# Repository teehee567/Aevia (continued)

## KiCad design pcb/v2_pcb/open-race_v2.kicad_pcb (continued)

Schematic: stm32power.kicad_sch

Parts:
C28, C36, C39, C40, C46, C47, C48, C50, C52, C54, C55, C58, C59, C64, C66, C67, C71, C72, C73, C74, C75, C76, C77, C78, C79, C80, C169, C309: 100nF 50V X7R; C_0402_1005Metric; Voltage 50 VDC; Tolerance ±10%; MPN CGA2B3X7R1H104K050BE
C29, C35: 10uF 10V X7R; C_0805_2012Metric; Voltage 10 VDC; Tolerance ±10%; MPN GCJ21BR71A106KE01L
C34: 4.7uF 16V X7S; C_0603_1608Metric; Voltage 16 VDC; Tolerance ±10%; MPN GCM188C71C475KE36D
C37: 2.2nF 50V X7R; C_0402_1005Metric; Voltage 50 VDC; Tolerance ±10%; MPN CGA2B2X7R1H222K050BE
C38, C41, C43, C44, C45, C51, C57, C60, C61, C63, C65, C68, C69, C70, C308: 1uF 10V X7S; C_0402_1005Metric; Voltage 10 VDC; Tolerance ±10%; MPN GCM155C71A105KE38D
C170, C176, C177, C178, C179: 22uF 6.3V X7T; C_0805_2012Metric; Voltage 6.3 VDC; Tolerance ±20%; MPN GCJ21BD70J226ME02L
L4: 2.2nH 1A; L_TDK_MHQ1005_1.0x0.6mm; MPN MHQ1005P2N2BT000
L7: 1uH; L_1008_2520Metric; MPN DFE252012P-1R0M=P2
L8: 22R @100MHz 8A; L_0603_1608Metric; MPN BLM18SN220TN1D
R22, R167: 0R; R_1206_3216Metric; Tolerance Jumper; MPN WFZ120600000ZE66
R27: 0R; R_0402_1005Metric; Tolerance Jumper; MPN RC0402JR-070RL
R148, R159: 0R; R_0402_1005Metric; Tolerance Jumper; MPN CRCW04020000Z0ED
R168: 50mR (DNP); R_2512_6332Metric
R173: 0R DNP (alternate to L8); R_0402_1005Metric
R220: 2R; R_0402_1005Metric; Tolerance ±1%; MPN RCS04022R00FKED
U1: STM32N657X0H3Q; VFBGA264_14X14_STM

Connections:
+1V8_AON: C36.2, R148.1; also elsewhere on the board
+1V8_RUN: C38.2, C39.2, C46.2, C47.2, C50.2, C54.2, C71.2, C74.2, C77.2, C78.2, C79.2, C80.2, L4.1, L8.1, R27.1, R173.2, U1.C5 (VDDA18USB), U1.L13 (VDDIO2), U1.L14 (VDDIO2), U1.M5 (VDDA18PLL), U1.M14 (VDDIO2), U1.M15 (VDDIO2), U1.N6 (VDDA18ADC), U1.N13 (VDDIO3), U1.P13 (VDDIO3), U1.R5 (VDDA18CSI); also elsewhere on the board
/STM32 power/I_SENS_VDDCORE_N: C170.1, R22.2, R167.1, R168.1, U1.G2 (VFBSMPS)
/STM32 power/I_SENS_VDDCORE_P: C170.2, C176.2, C177.1, C178.2, C179.2, L7.2, R167.2, R168.2
unnamed: C29.1, C35.1, C41.1, C45.1, C48.1, C52.1, L4.2, U1.K1 (VDDSMPS), U1.K2 (VDDSMPS), U1.K3 (VDDSMPS), U1.K4 (VDDSMPS), U1.K5 (VDDSMPS), U1.K6 (VDDSMPS)
unnamed: C37.1, R220.2
unnamed: L7.1, R220.1, U1.J1 (VLXSMPS), U1.J2 (VLXSMPS), U1.J3 (VLXSMPS), U1.J4 (VLXSMPS), U1.J5 (VLXSMPS), U1.J6 (VLXSMPS)
unnamed: C34.1, U1.F1 (V08CAP)
unnamed: C43.2, R159.2, U1.A4 (VDD33USB)
VDDA18AON: C40.2, R148.2, U1.F6 (VDDA18AON)
VDDA18PMU: C169.2, L8.2, R173.1, U1.G1 (VDDA18PMU)
VDDCORE: C44.2, C51.2, C57.2, C60.2, C61.2, C63.2, C65.2, C68.2, C69.2, C70.2, R22.1, U1.L6 (VDDCORE), U1.L12 (VDDCORE), U1.M7 (VDDCORE), U1.M9 (VDDCORE), U1.M11 (VDDCORE), U1.N8 (VDDCORE), U1.N10 (VDDCORE), U1.N12 (VDDCORE), U1.P11 (VDDCORE), U1.R4 (VDDCSI)
VREFP: C308.1, C309.1, R27.2, U1.U2 (VREF+)

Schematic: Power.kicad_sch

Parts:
C7, C11, C14, C83, C86, C187, C190, C240, C246, C249, C252: 100nF 50V X7R; C_0603_1608Metric; Voltage 50 VDC; Tolerance ±10%; MPN CGA3E2X7R1H104K080AE
C8, C12, C18: 10nF 50V X7R; C_0603_1608Metric; Voltage 50 VDC; Tolerance ±10%; MPN CGA3E2X7R1H103K080AE
C9, C10, C42, C56, C62, C81, C82, C84, C85, C87, C88, C91, C93, C233, C234: 10uF 50V X7R; C_1210_3225Metric; Voltage 50 VDC; Tolerance ±10%; MPN CNA6P1X7R1H106K250AE
C13, C15, C16, C17: 470nF 25V X7R; C_0603_1608Metric; Voltage 25 VDC; Tolerance ±10%; MPN CGA3E3X7R1E474K080AE
C49, C53: 47nF 50V X7R; C_0603_1608Metric; Voltage 50 VDC; Tolerance ±10%; MPN CGA3E2X7R1H473K080AE
C92, C251: 4.7uF 16V X7R; C_0805_2012Metric; Voltage 16 VDC; Tolerance ±10%; MPN CGA4J3X7R1C475K125AE
C180: 10uF 25V X7R; C_1206_3216Metric; Voltage 25 VDC; Tolerance ±10%; MPN CGA5L1X7R1E106K160AE
C181, C188, C189: 22uF 10V X7R; C_1206_3216Metric; Voltage 10 VDC; Tolerance ±10%; MPN GCJ31CR71A226KE01L
C182: 22pF 50V C0G; C_0603_1608Metric; Voltage 50 VDC; Tolerance ±5%; MPN CGA3E2C0G1H220J080AA
C186, C236, C237, C238: 22uF 25V X7R; C_1210_3225Metric; Voltage 25 VDC; Tolerance ±20%; MPN CGA6P3X7R1E226M250AE
C191, C244: 1uF 25V X7R; C_0603_1608Metric; Voltage 25 VDC; Tolerance ±10%; MPN CGA3E1X7R1E105K080AE
C192: 3.9nF 100V C0G; C_0603_1608Metric; Voltage 100 VDC; Tolerance ±5%; MPN CGA3E1C0G2A392J080AE
C235, C239: 10uF 25V X7S; C_0805_2012Metric; Voltage 25 VDC; Tolerance ±10%; MPN GCJ21BC71E106KE02L
C241, C242, C243: 1nF 100V C0G; C_0603_1608Metric; Voltage 100 VDC; Tolerance ±5%; MPN CGA3E2C0G2A102J080AE
C245, C248: 10uF 10V X7R; C_0805_2012Metric; Voltage 10 VDC; Tolerance ±10%; MPN GCJ21BR71A106KE01L
C247, C250: 1uF 50V X7R; C_0805_2012Metric; Voltage 50 VDC; Tolerance ±10%; MPN CGA4J3X7R1H105K125AE
D2: ASMT-RF45-AN002 YELLOW GREEN; LED_0603_1608Metric; MPN ASMT-RF45-AN002
F1: 5.0A Ihold @23C / 24V PTC; Fuse_2920_7451Metric; MPN 2920L500/24SLDR
FB20, FB21: 600Ω @ 100MHz, 1.4A AEC-Q200; FB_Murata_BLM21_2.0x1.25mm; MPN BLM21PG601SH1D
J20: 2S_PACK_BALANCE; Molex_Micro-Fit_3.0_43650-0300_1x03_P3.00mm_Horizontal; MPN 43650-0300
L1: 2.2uH XAL7030-222MEC; L_Coilcraft_XAL7030-222; MPN XAL7030-222MEC
L20: 1.5uH XFL4020-152MEC; L_Coilcraft_XxL4020; MPN XFL4020-152MEC
NTC1: NCP15XH103F03RC; R_0402_1005Metric; MPN NCP15XH103F03RC
NTC2: NCP15XH103F03RC 10k B3380; R_0402_1005Metric; MPN NCP15XH103F03RC
Q3, Q4, Q5: CSD18540Q5B; VSON-CLIP-8_DNK_5x6mm; MPN CSD18540Q5B
R6, R9, R222: 1k; R_0603_1608Metric; Tolerance ±1%; MPN CRCW06031K00FKEA
R7, R8, R23: 100; R_0603_1608Metric; Tolerance ±1%; MPN CRCW0603100RFKEA
R10: 10; R_0603_1608Metric; Tolerance ±1%; MPN CRCW060310R0FKEA
R11, R12: 68; R_1206_3216Metric; Tolerance ±1%; MPN CRCW120668R0FKEAHP
R13: 5m 1% 1W; R_2512_6332Metric; Tolerance ±1%; MPN WSL2512R0050FEA
R20: 100R 1%; R_0603_1608Metric; Tolerance 1%; MPN CRCW0603100RFKEA
R24, R29, R30, R31, R37, R38, R39, R221, R240: 10k; R_0603_1608Metric; Tolerance ±1%; MPN CRCW060310K0FKEA
R25: 5.23k 1%; R_0603_1608Metric; Tolerance ±1%; MPN CRCW06035K23FKEA
R26: 30.1k 1%; R_0603_1608Metric; Tolerance ±1%; MPN CRCW060330K1FKEA
R28: 2k2; R_0603_1608Metric; Tolerance ±1%; MPN CRCW06032K20FKEA
R35: 8.2k; R_0603_1608Metric; Tolerance ±1%; MPN CRCW06038K20FKEA
R223: 47k 1%; R_0603_1608Metric; Tolerance ±1%; MPN CRCW060347K0FKEA
R224: 37.4k 1%; R_0603_1608Metric; Tolerance ±1%; MPN CRCW060337K4FKEA
R228: 220k; R_0603_1608Metric; Tolerance ±1%; MPN CRCW0603220KFKEA
R229, R244, R245, R246, R247, R248: 100k; R_0603_1608Metric; Tolerance ±1%; MPN CRCW0603100KFKEA
TP1: TestPoint_Small; TestPoint_Pad_D1.0mm
TP20: AUX5_PG; TestPoint_Pad_D1.0mm
U6: BQ25798RQMR; IC_BQ25798RQMR; PARTREV B
U7: MAX17320G22+; TQFN-24-1EP_4x4mm_P0.5mm_EP2.6x2.6mm; MPN MAX17320G22+
U8: RPL-3.0-R; LGA-10_RECOM_RPL-3.0_3x3mm; MPN RPL-3.0-R
U10: TPSM863253RDXR; Texas_RDX0007A_QFN-FCMOD-7-3.3x4mm-P0.5mm_4EP_NoVias; MPN TPSM863253RDXR
U11: TPS22997RYZR; Texas_RYZ0010A_WQFN-HR-10_2x1.5mm_P0.5mm; MPN TPS22997RYZR
U20: TPS630701RNMR (5V fixed); VQFN-HR-15_RNM_2.5x3mm_P0.5mm; MPN TPS630701RNMR
U21, U22, U23: TPS22918DBVR; SOT-23-6_DBV; MPN TPS22918DBVR

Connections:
+1V8_AON: C181.1, C182.1, C191.1, R222.2, R223.1, U8.5 (VOUT), U11.2 (VIN), U11.3 (VIN); also elsewhere on the board
+1V8_RUN: U11.6 (QOD), U11.7 (VOUT), U11.8 (VOUT); also elsewhere on the board
+3V3_GNSS_CLEAN: C248.1, C249.1, FB20.1; also elsewhere on the board
+3V3_IMU_CLEAN: C251.1, C252.1, FB21.1; also elsewhere on the board
+3V3_RADIO_SW: C245.1, C246.1, U21.5 (QOD), U21.6 (VOUT); also elsewhere on the board
+5V_AUX: C236.1, C237.1, C238.1, C239.1, U20.5 (FB), U20.7 (VOUT), U20.8 (VOUT); also elsewhere on the board
/Power/AUX5_EN: R244.1, U20.14 (EN); also elsewhere on the board
/Power/AUX_SW1: L20.2, U20.11 (L1)
/Power/AUX_SW2: L20.1, U20.9 (L2)
/Power/AUX_VAUX: C240.1, U20.3 (VAUX)
/Power/BAT_ALRT: R37.1, U7.7 (ALRT); also elsewhere on the board
/Power/BQ_BATP_SENSE: R23.1, U6.18 (BATP)
/Power/BQ_BTST1: C49.2, U6.4 (BTST1)
/Power/BQ_BTST2: C53.2, U6.19 (BTST2)
/Power/BQ_PMID: C86.2, C87.2, C88.2, C91.2, U6.29 (PMID)
/Power/BQ_PROG_SET: R35.2, U6.20 (PROG)
/Power/BQ_QON_TP: TP1.1 (1_1), U6.12 (~QON)
/Power/BQ_STAT: R28.1, U6.1 (STAT)
/Power/BQ_STAT_LED: D2.1 (K), R28.2
/Power/BQ_SW1: C49.1, L1.1, U6.28 (SW1)
/Power/BQ_SW2: C53.1, L1.2, U6.26 (SW2)
/Power/BUCK_3V3_EN: R228.2, R229.1, U10.6 (EN)
/Power/BUCK_3V3_PG: R221.2, U8.1 (CTRL), U10.5 (PG); also elsewhere on the board
/Power/CELL_MID: J20.2, R12.1
/Power/CHG_INT: R31.1, U6.21 (~INT); also elsewhere on the board
/Power/GNSS_EN: R247.1, U22.3 (ON); also elsewhere on the board
/Power/GNSS_EN_CT: C242.1, U22.4 (CT)
/Power/GNSS_SW_RAW: C247.1, FB20.2, U22.5 (QOD), U22.6 (VOUT)
/Power/IMU_EN: R248.1, U23.3 (ON); also elsewhere on the board
/Power/IMU_EN_CT: C243.1, U23.4 (CT)
/Power/IMU_SW_RAW: C250.1, FB21.2, U23.5 (QOD), U23.6 (VOUT)
/Power/MAX_AOLDO: C17.1, U7.12 (AOLDO)
/Power/MAX_CELL1_SENSE: C8.2, C12.1, R12.2, U7.21 (CELL1)
/Power/MAX_IN_SENSE: C13.2, C14.1, R10.2, U7.1 (IN)
/Power/MAX_REG2: C16.1, U7.17 (REG2)
/Power/MAX_REG3: C15.1, U7.13 (REG3)
/Power/MAX_TH1_NTC: NTC1.2, U7.10 (TH1)
/Power/MAX_TOP_SENSE: C8.1, R11.2, U7.22 (CELL2), U7.23 (CELL3), U7.24 (BATTS)
/Power/PACK_POS: C7.1, F1.2, Q4.1 (S), Q4.2 (S), Q4.3 (S), R10.1, R11.1
/Power/PACK_POS_CONN: F1.1, J20.1
/Power/PMIC_SCL: R30.1, R39.1, U6.14 (SCL), U7.8 (SCL/OD); also elsewhere on the board
/Power/PMIC_SDA: R29.1, R38.1, U6.15 (SDA), U7.9 (SDA/DQ); also elsewhere on the board
/Power/PWR_ON: U11.10 (ON); also elsewhere on the board
/Power/RADIO_EN: R246.1, U21.3 (ON); also elsewhere on the board
/Power/REGN: C92.2, R24.2, R25.1, U6.5 (REGN)
/Power/RPL_FB: C182.2, R223.2, R224.1, U8.7 (FB)
/Power/RPL_SENSE: R222.1, U8.6 (+Sense)
/Power/RUN_QOD: C192.1, U11.9 (CT)
/Power/vpack+: Q3.5 (D), Q3.6 (D), Q3.7 (D), Q3.8 (D), Q5.1 (S), Q5.2 (S), Q5.3 (S), R6.1, R23.2, R240.1
GND1: C12.2, C14.2, C15.2, C16.2, C17.2, C18.2, J20.3, NTC1.1, R9.1, R13.1, U7.15 (CSP), U7.16 (TH2), U7.18 (TH3), U7.19 (TH4), U7.20 (GND), U7.25 (EPAD)
unnamed: C84.1, C85.1, Q3.1 (S), Q3.2 (S), Q3.3 (S), U6.22 (BAT), U6.23 (BAT)
unnamed: Q3.4 (G), R20.2
unnamed: Q4.5 (D), Q4.6 (D), Q4.7 (D), Q4.8 (D), Q5.5 (D), Q5.6 (D), Q5.7 (D), Q5.8 (D)
unnamed: C7.2, Q4.4 (G), R7.1
unnamed: Q5.4 (G), R8.1
unnamed: R24.1, U6.17 (ILIM_HIZ)
unnamed: R20.1, U6.24 (SDRV)
unnamed: NTC2.1, R25.2, R26.2, U6.16 (TS)
unnamed: R7.2, U7.3 (CHG)
unnamed: C13.1, U7.2 (CP)
unnamed: R8.2, U7.4 (DIS)
unnamed: C18.1, R6.2, U7.6 (PCKP)
unnamed: R9.2, U7.11 (PFAIL)
unnamed: R240.2, U7.5 (ZVC)
unnamed: R245.2, TP20.1 (1_1), U20.2 (PG)
unnamed: C241.1, U21.4 (CT)
VBUS_PD: C9.2, C10.2, C11.2, C42.2, U6.2 (VBUS), U6.3 (VBUS), U6.8 (VAC2), U6.9 (VAC1); also elsewhere on the board
VSYS_RAW: C56.2, C62.2, C81.2, C82.2, C83.2, C93.2, C180.1, C186.1, C187.1, C233.1, C234.1, C235.1, R228.1, U6.25 (SYS), U8.2 (VIN), U10.1 (VIN), U20.12 (VIN), U20.13 (VIN)

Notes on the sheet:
3V3 branches: RADIO load-switched; GNSS/IMU load-switched then C-FB-C filtered.
5 V AUX: TPS630701 fixed buck-boost; AUX5_EN controls EN; power-save mode selected.
POWER TREE — REGULATOR STAGES VSYS_RAW -> U10 (3.3 V) -> +3V3_MAIN; open-drain PG drives BUCK_3V3_PG. VSYS_RAW -> U8 (1.8 V) -> +1V8_AON; CTRL = BUCK_3V3_PG with +3V3_MAIN pull-up. VSYS_RAW -> U20 (fixed 5 V buck-boost) -> +5V_AUX; AUX5_EN controls EN. Validate all rails across the approved loaded 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
1.8 V RUN LOAD SWITCH — TPS22997RYZR
+1V8_AON -> U11 -> +1V8_RUN; ON = STM32 PWR_ON. C192 = 3.9nF: about 1.05ms 10–90% rise at 1.8V. QOD tied to VOUT for fast discharge; PG unused.
COMMISSIONING - BQ25798: RPROG=8.2k selects 2S / 750kHz at POR; charge current remains at the 1A default until firmware raises it only after thermal and cell checks pass.
VBUS HOT-PLUG: TVS2200 clamps VBUS_PD and populated 2.2R/2.2uF snubber damps cable ringing; scope and tune after worst-cable testing. TVS2200 is for SPR <=20V / 21V ceiling only - never enable 28V EPR.
PMIC_SCL/SDA direct host link is valid across only R13=5mOhm Kelvin shunt; preserve GND1 (cell/CSP) / GND (system/CSN) separation and do not bridge elsewhere.
COMMISSIONING - MAX17320 NVM: before enabling charge, program and validate nPackCfg for 2S (NCELLS=0), one 10k TH1, nRSense=5mOhm, and the selected 21700 cell model/capacity/protection limits. Wiring alone does not define these settings.
PACK TEMPERATURE: initial build must thermally couple both NTC1 (MAX17320 TH1) and fitted NTC2 (BQ25798 TS) to the pack. Keep BQ TS_IGNORE=0; configure MAX for the NCP15 10k/B3380 model; validate hot/cold thresholds before raising charge current.
MAX17320 2S: CELL1=cell midpoint; CELL2=CELL3=BATTS=filtered pack top, per datasheet Figure 24 / Note 10.
1.8 V AON BUCK — RPL-3.0-R
5 V AUX BUCK-BOOST — TPS630701RNMR
3.3 V MAIN BUCK — TPSM863253RDXR
U10: SW pin 2 DNC; VOS pin 7 to VOUT. EN 220k/100k (2M internal pull-down): ~4.14V turn-on, EN <=5.14V at VIN=17V.
PRE-LAYOUT HOLD: verify Q1-Q5/F1 current, SOA, copper, thermal vias and connector temperature rise at worst-case charge/load current.

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
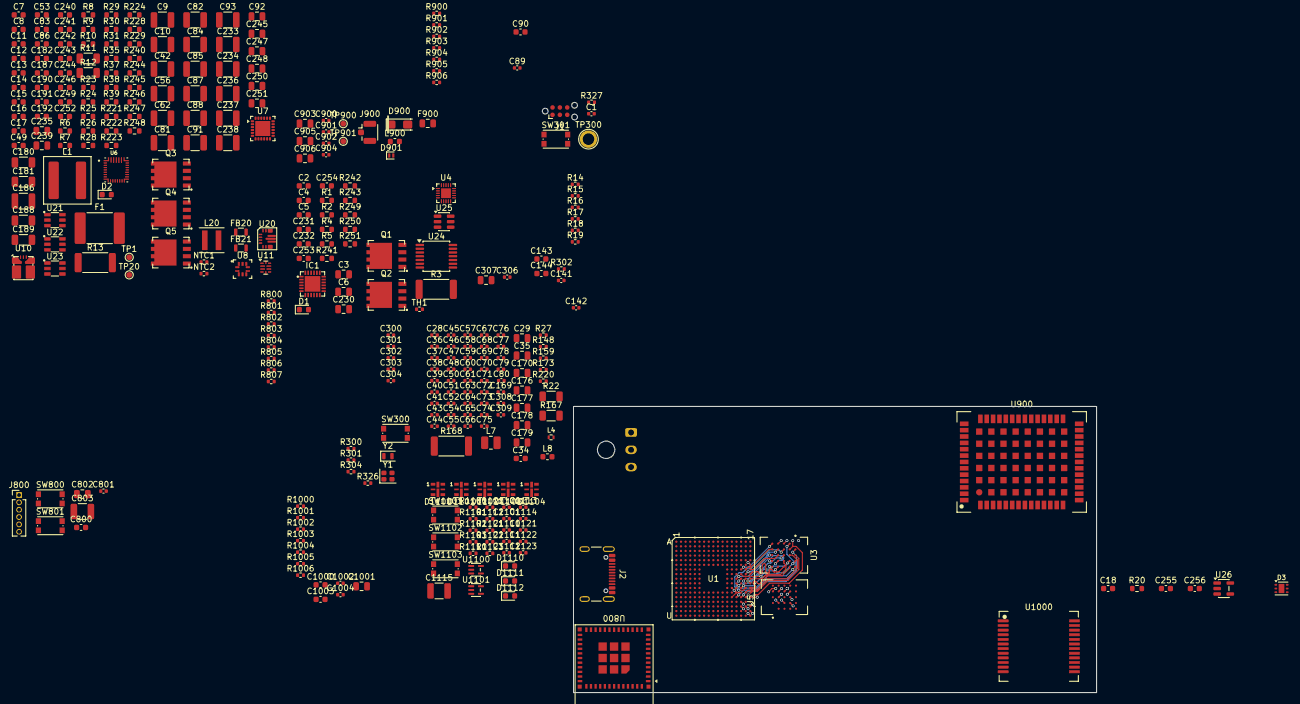
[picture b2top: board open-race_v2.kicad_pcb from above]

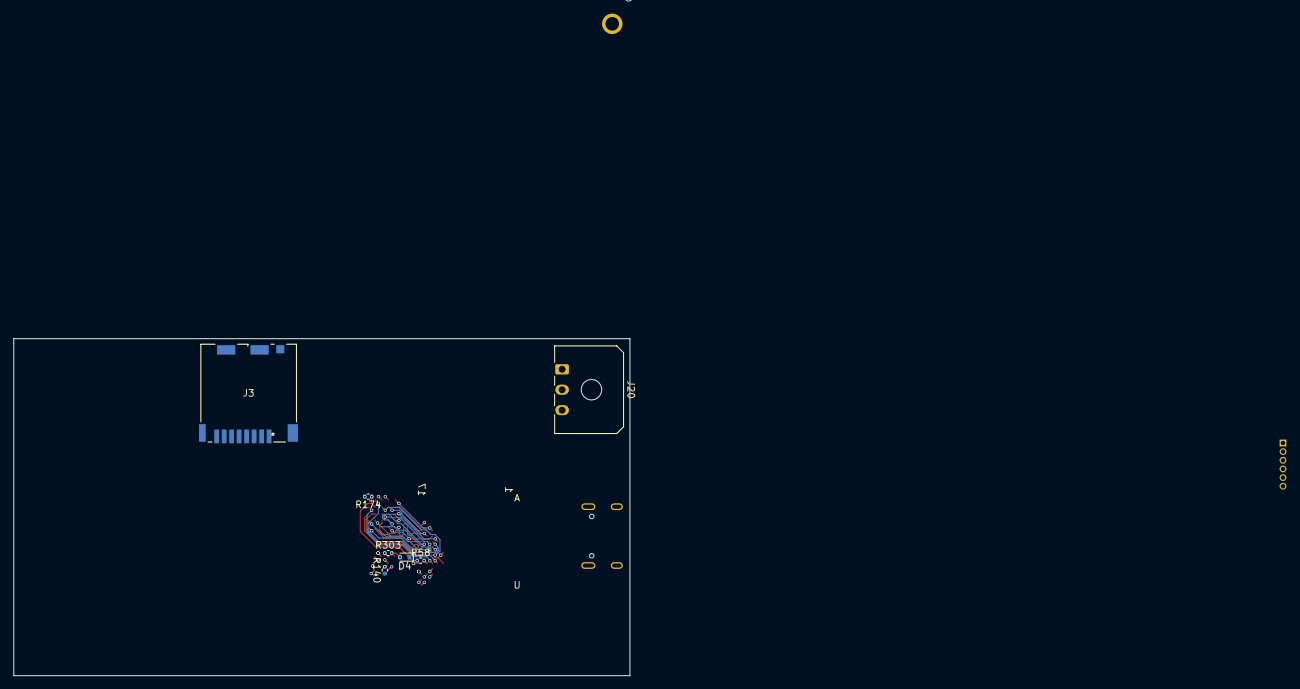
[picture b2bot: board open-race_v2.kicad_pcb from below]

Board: 8 copper layers, 90.5 x 49.5 mm, 337 parts (7 on the bottom side), 225 nets.

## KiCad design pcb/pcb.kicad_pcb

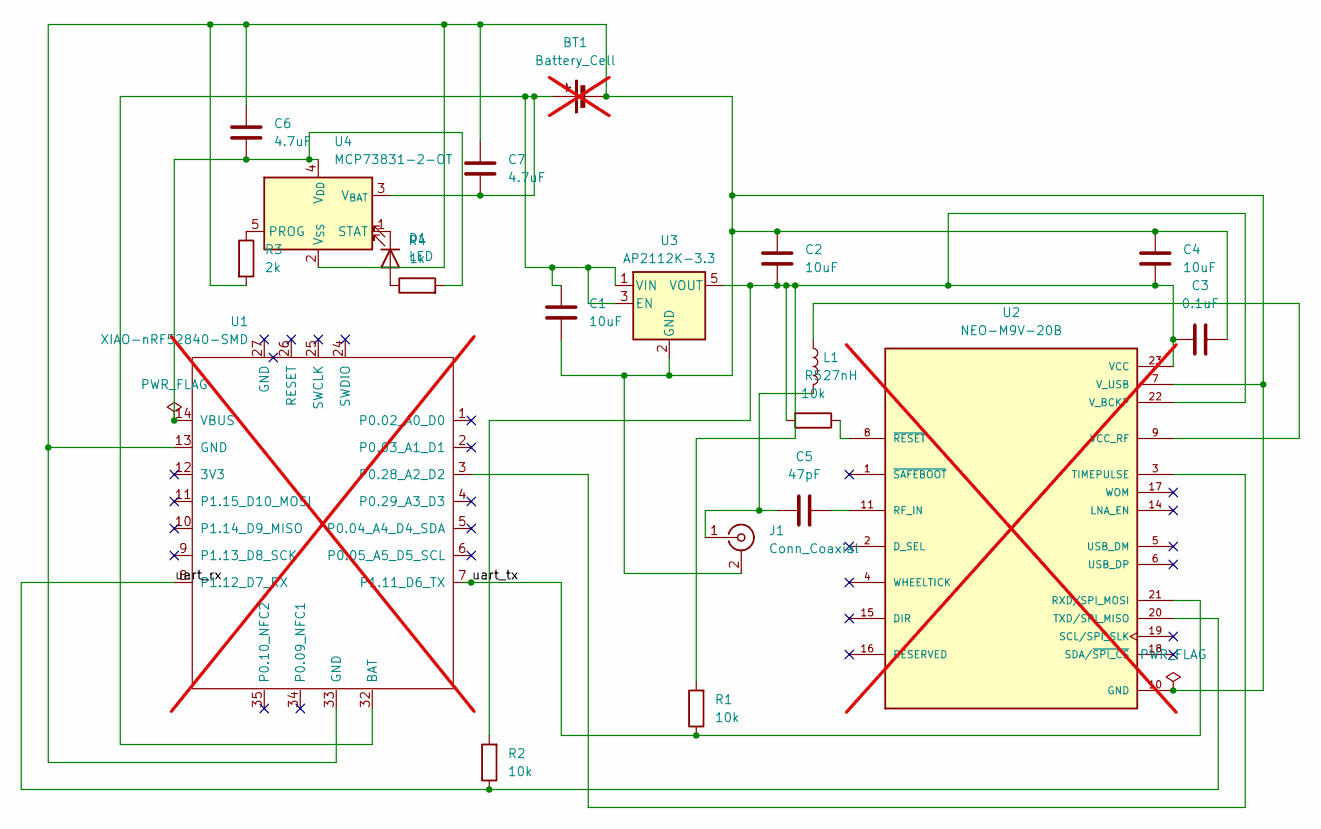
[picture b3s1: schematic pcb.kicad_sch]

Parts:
BT1: Battery_Cell; JST_PH_S2B-PH-K_1x02_P2.00mm_Horizontal; not fitted
C1, C2, C4: 10uF; C_0805_2012Metric; LCSC GRM21BC71C106KE11L
C3: 0.1uF; C_0805_2012Metric; LCSC C0805C104K5RACTU
C5: 47pF; C_0402_1005Metric; LCSC GRM1555C1H470JA01D
C6, C7: 4.7uF; C_0805_2012Metric; LCSC CL21A475KAQNNNE
D1: LED; LED_0805_2012Metric; LCSC 150080VS75000
J1: Conn_Coaxial; U.FL_Molex_MCRF_73412-0110_Vertical; LCSC U.FL-R-SMT-1(10)
L1: 27nH; L_0402_1005Metric; LCSC LQG15HN27NJ02D
R1, R2, R5: 10k; R_0805_2012Metric; LCSC RC0805FR-0710KL
R3: 2k; R_0805_2012Metric; LCSC RC0805FR-072KL
R4: 1k; R_0805_2012Metric; LCSC RC0805FR-071KL
U1: XIAO-nRF52840-SMD; LCSC 102010448; not fitted
U2: NEO-M9V-20B; XCVR_NEO-M9V-20B; PARTREV C1; LCSC NEO-M9V-20B; not fitted
U3: AP2112K-3.3; SOT-23-5; LCSC AP2112K-3.3TRG1
U4: MCP73831-2-OT; SOT-23-5; LCSC MCP73831T-2ACI/OT

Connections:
/uart_rx: R2.1, U1.8 (P1.12_D7_RX), U2.20 (TXD/SPI_MISO)
/uart_tx: R1.1, U1.7 (P1.11_D6_TX), U2.21 (RXD/SPI_MOSI)
GND: BT1.2 (-), C1.2, C2.2, C3.1, C4.2, C6.1, C7.1, J1.2 (Ext), R3.2, U1.13 (GND), U1.33 (GND), U2.7 (V_USB), U2.10 (GND), U2.12 (GND), U2.13 (GND), U2.24 (GND), U3.2 (GND), U4.2 (V_{SS})
unnamed: BT1.1 (+), C1.1, C7.2, U1.32 (BAT), U3.1 (VIN), U3.3 (EN), U4.3 (V_{BAT})
unnamed: D1.2 (A), R4.1
unnamed: D1.1 (K), U4.1 (STAT)
unnamed: C5.1, J1.1 (In), L1.2
unnamed: U1.3 (P0.28_A2_D2), U2.3 (TIMEPULSE)
unnamed: C6.2, R4.2, U1.14 (VBUS), U4.4 (V_{DD})
unnamed: C5.2, U2.11 (RF_IN)
unnamed: C2.1, C3.2, C4.1, R1.2, R2.2, R5.2, U2.22 (V_BCKP), U2.23 (VCC), U3.5 (VOUT)
unnamed: L1.1, U2.9 (VCC_RF)
unnamed: R5.1, U2.8 (~RESET)
unnamed: R3.1, U4.5 (PROG)

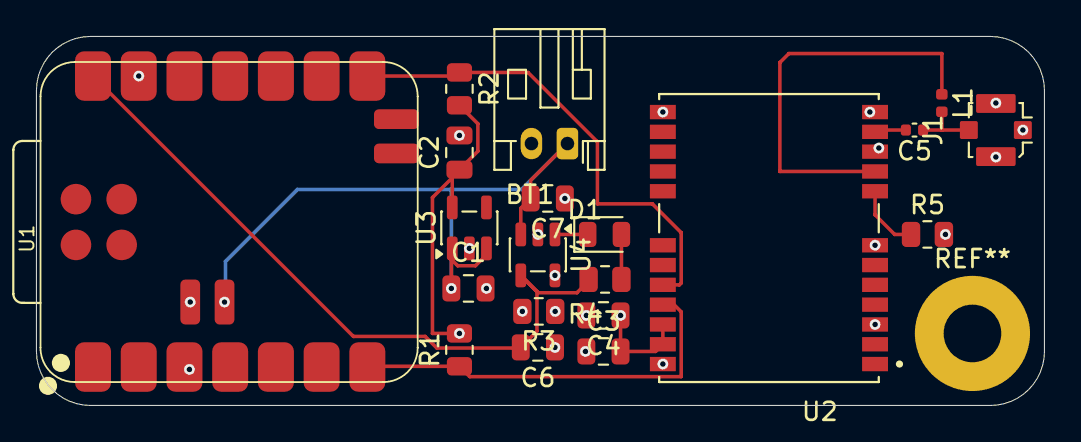
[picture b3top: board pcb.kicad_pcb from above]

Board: 4 copper layers, 56.0 x 20.5 mm, 20 parts (0 on the bottom side), 14 nets.

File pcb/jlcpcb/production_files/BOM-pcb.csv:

Comment,Designator,Footprint,LCSC,Quantity
0.1uF,C3,C_0805_2012Metric,C1525,1
10k,"R1,R2,R5",R_0805_2012Metric,C17414,3
10uF,"C1,C2,C4",C_0805_2012Metric,C440198,3
1k,R4,R_0805_2012Metric,C17513,1
27nH,L1,L_0402_1005Metric,C115488,1
2k,R3,R_0805_2012Metric,C17604,1
4.7uF,"C6,C7",C_0805_2012Metric,C1779,2
47pF,C5,C_0402_1005Metric,C1567,1
LED,D1,LED_0805_2012Metric,C34499,1

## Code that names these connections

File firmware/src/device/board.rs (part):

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        // Inventory only: erasing pin types performs no GPIO configuration.
        // Each connection below takes its owner using the HAL wiring constant.
        let mut pins = Pins([
            Some(p.GPIO0.degrade()),
            Some(p.GPIO1.degrade()),
            Some(p.GPIO2.degrade()),
            Some(p.GPIO3.degrade()),
            Some(p.GPIO4.degrade()),
            Some(p.GPIO5.degrade()),
            Some(p.GPIO6.degrade()),
            Some(p.GPIO7.degrade()),
            Some(p.GPIO8.degrade()),
            Some(p.GPIO9.degrade()),
            Some(p.GPIO10.degrade()),
            Some(p.GPIO11.degrade()),
            Some(p.GPIO12.degrade()),
            Some(p.GPIO13.degrade()),
            Some(p.GPIO14.degrade()),
            Some(p.GPIO15.degrade()),
            Some(p.GPIO16.degrade()),
            Some(p.GPIO17.degrade()),
            Some(p.GPIO18.degrade()),
            Some(p.GPIO19.degrade()),
            Some(p.GPIO20.degrade()),
            Some(p.GPIO21.degrade()),
            Some(p.GPIO22.degrade()),
            Some(p.GPIO23.degrade()),
            Some(p.GPIO24.degrade()),
            Some(p.GPIO25.degrade()),
            Some(p.GPIO26.degrade()),
            Some(p.GPIO27.degrade()),
            Some(p.GPIO28.degrade()),
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            Some(p.GPIO30.degrade()),
            Some(p.GPIO31.degrade()),
            Some(p.GPIO32.degrade()),
            Some(p.GPIO33.degrade()),
            Some(p.GPIO34.degrade()),
            Some(p.GPIO35.degrade()),
            Some(p.GPIO36.degrade()),
            Some(p.GPIO37.degrade()),
            Some(p.GPIO38.degrade()),
            Some(p.GPIO39.degrade()),
            Some(p.GPIO40.degrade()),
            None, // No GPIO41 owner in the S31 SDK.
            Some(p.GPIO42.degrade()),
            Some(p.GPIO43.degrade()),
            Some(p.GPIO44.degrade()),
            Some(p.GPIO45.degrade()),
            Some(p.GPIO46.degrade()),
            Some(p.GPIO47.degrade()),
            Some(p.GPIO48.degrade()),
            Some(p.GPIO49.degrade()),
            Some(p.GPIO50.degrade()),
            Some(p.GPIO51.degrade()),
            Some(p.GPIO52.degrade()),
            Some(p.GPIO53.degrade()),
            Some(p.GPIO54.degrade()),
            Some(p.GPIO55.degrade()),
            Some(p.GPIO56.degrade()),
            Some(p.GPIO57.degrade()),
            Some(p.GPIO58.degrade()),
            Some(p.GPIO59.degrade()),
            Some(p.GPIO60.degrade()),
            Some(p.GPIO61.degrade()),
        ]);
        let power_bus = native::init_power_i2c(
            p.I2C0,
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        let recording_slot = sd
            .slot::<0>(Default::default())
            .expect("SD slot")
            .with_clk(GPIO24::try_from(pins.take(wiring::sd::CLK)).expect("SD CLK wiring"))
            .with_cmd(GPIO25::try_from(pins.take(wiring::sd::CMD)).expect("SD CMD wiring"))
            .with_data0(GPIO20::try_from(pins.take(wiring::sd::DATA[0])).expect("SD D0 wiring"))
            .with_data1(GPIO21::try_from(pins.take(wiring::sd::DATA[1])).expect("SD D1 wiring"))
            .with_data2(GPIO22::try_from(pins.take(wiring::sd::DATA[2])).expect("SD D2 wiring"))
            .with_data3(GPIO23::try_from(pins.take(wiring::sd::DATA[3])).expect("SD D3 wiring"));
        // MAX16169 active-low kill is released; retain its owner for application life.
        let power_hold = Output::new(
            pins.take(wiring::power::KILL_N),
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
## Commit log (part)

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2026-04-04 add ignore
2026-04-04 update ignore
2026-04-04 add pcb base
2026-04-05 first version pcb done
2026-04-05 added schematics and auto build
2026-04-05 pcb printed
2026-04-05 init cargo
2026-04-07 recover schematics
2026-04-18 Update pcb from remove safeboot pull up
2026-04-20 update image
2026-04-26 basic blinking lights with full embedded loader
2026-04-26 disable xiao charging
2026-04-26 use heap init macro
2026-04-26 update v2 plan
2026-04-27 add auto reboot like arduino
2026-04-27 abstract led out
2026-04-27 fix flash again
2026-04-27 Add status leds
2026-04-27 add detail to v2 pcb plan
2026-04-28 update goals
2026-04-28 update hardware overview
2026-04-30 add to readme
2026-04-30 fix readme
2026-05-18 move design notes to new doc
2026-05-18 power done
2026-05-18 leds
2026-05-18 usb c protection
2026-05-18 ldos
2026-05-18 update stm
2026-05-18 bruh
2026-05-18 add crystals
2026-05-18 change storage
2026-05-19 forgor
2026-05-19 change mpu again
2026-05-21 start on power schematic
2026-05-22 refactor for um980
2026-05-22 add accel test
2026-05-22 test host script
2026-05-23 sdlkfjl
2026-05-29 change imu
2026-06-03 start pcb v2
2026-06-03 add io pinouts
2026-06-03 add ram
2026-06-03 fix ram
2026-06-06 edit design
2026-06-06 edit emmc
2026-06-06 contineu pcb
2026-06-06 fix powertree
2026-06-13 add debug to pcb
2026-06-14 add usb to schematic
2026-06-19 change batter guage/protection
2026-06-19 add imu details
2026-06-19 add battery changes
2026-06-21 finish battery charger
2026-06-21 start on battery safety
2026-06-30 design component change
